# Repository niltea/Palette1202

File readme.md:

# Nilgiri12-02EC

English follows Japanese.

--------------------

Nilgiri12-02ECは、イラストレーターのための左手デバイスです。  
[Clip studio Paint](https://www.clipstudio.net) や、 [Adobe Photoshop](https://www.adobe.com/jp/products/photoshop.html)を使用した描画を快適に行うため設計されています。  
各種ショートカットを使用するためのキーを備えていることはもちろん、  
つまみを操作することで、ブラシサイズの変更やキャンバスの拡大・縮小等を快適に行うことができます。

コンパクトなサイズに設計されているため、持ち運んでの使用にも便利なだけでなく、  
据え置き環境で大型の液晶タブレットと一緒に使っても邪魔になりません。

また、オプションの電池キットを追加することで[BLE Micro Pro](https://yushakobo.jp/shop/ble-micro-pro/)にも対応するため、  
持ち運びの際でもケーブルが煩わしくありません。

Windows/Mac・Clip Studio / Photoshopの切替を行う事ができるため、  
PC・Macはもちろん、iPadでも同じ操作感で描画することができます。

--------------------

Nilgiri12-02EC is a lefthand-devece for illustrators. 
Designed for comfotablly drawing on [Clip studio Paint](https://www.clipstudio.net) / [Adobe Photoshop](https://www.adobe.com/jp/products/photoshop.html).

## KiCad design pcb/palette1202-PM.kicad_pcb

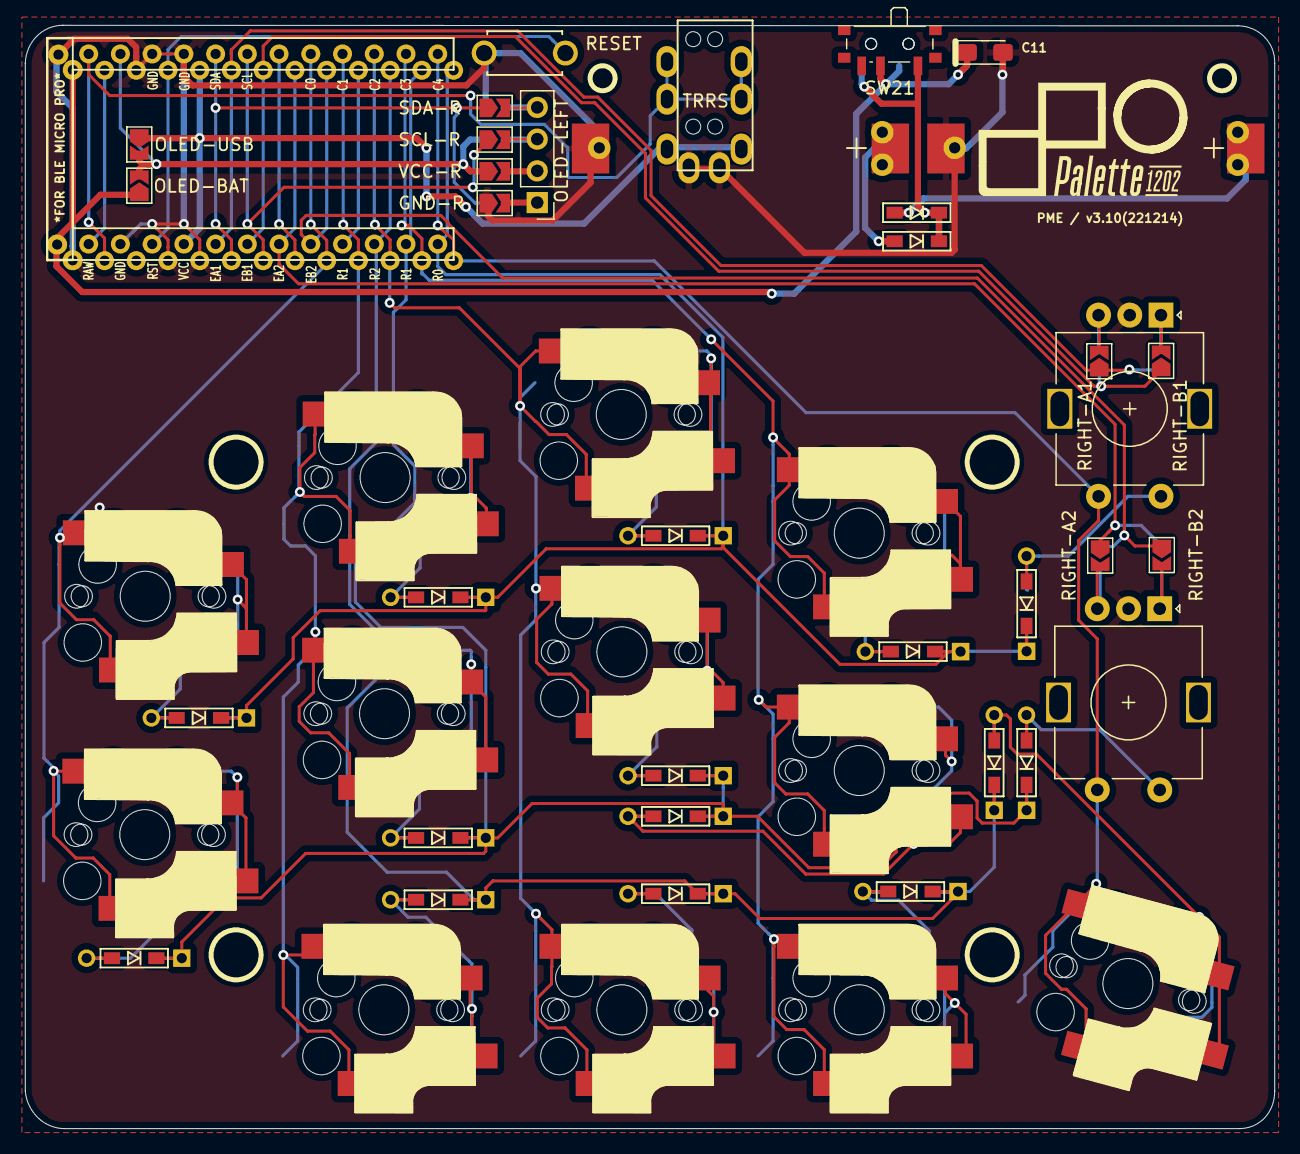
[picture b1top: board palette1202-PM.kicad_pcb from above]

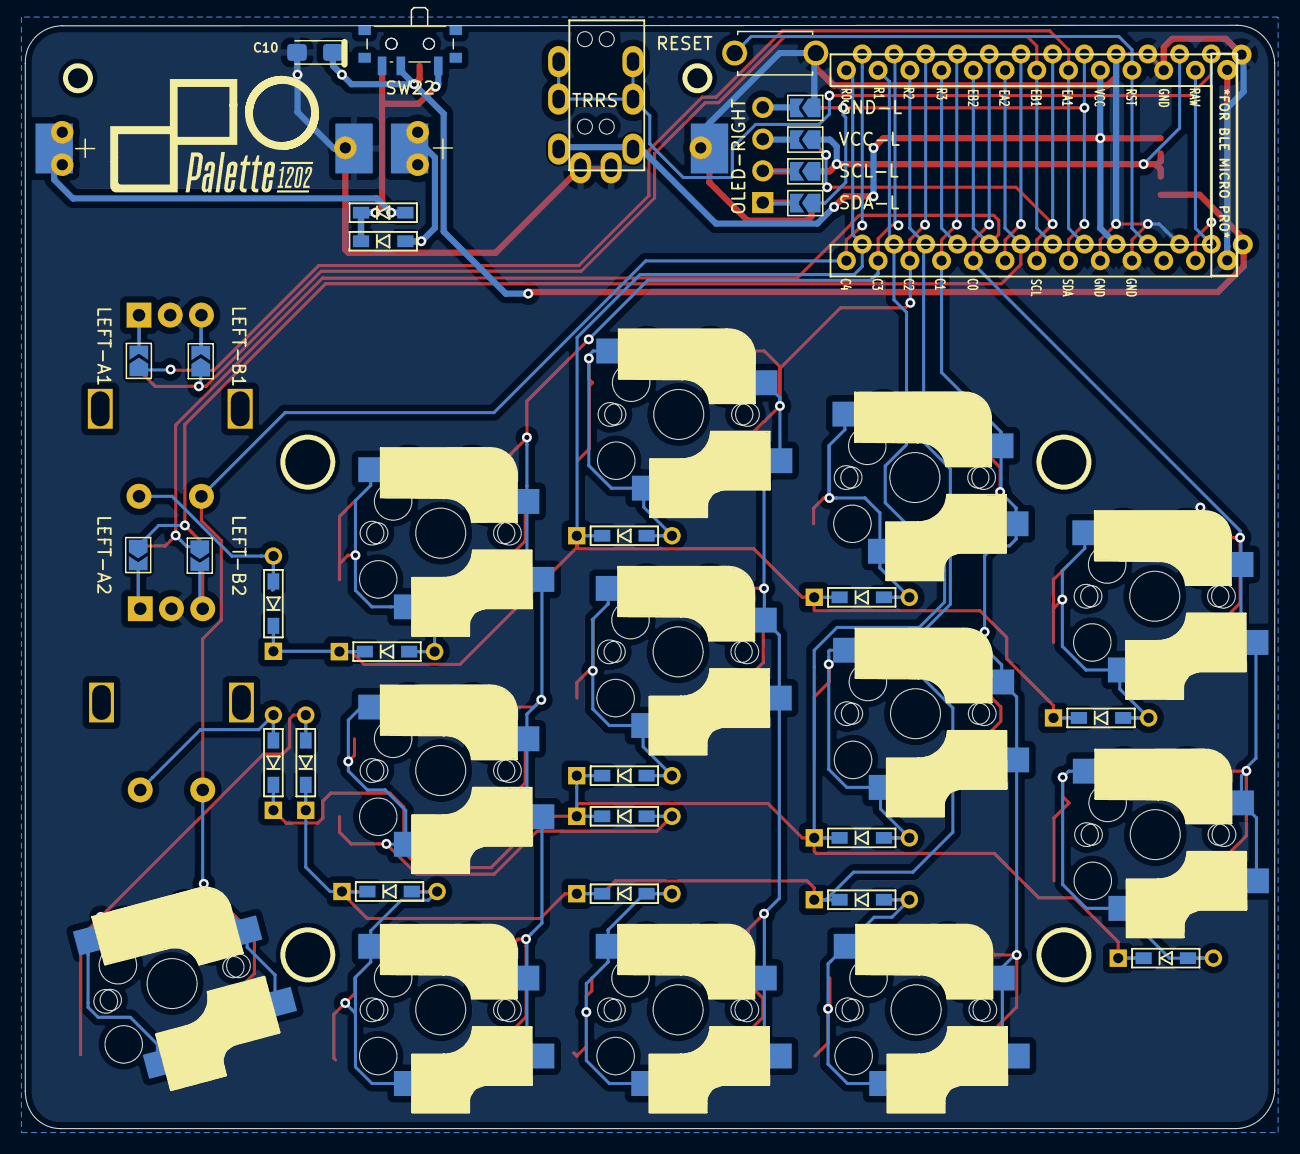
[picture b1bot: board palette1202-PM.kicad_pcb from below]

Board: 2 copper layers, 100.0 x 88.3 mm, 68 parts (26 on the bottom side), 45 nets.

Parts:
BT1, BT2: 3V; HU1632
C10, C11: 100u; CP_EIA-3216-10_Kemet-I_Pad1.58x1.35mm_HandSolder
D1, D2, D3, D4, D5, D6, D7, D8, D9, D10, D11, D12, D13, D14: 1N4148W; D3_TH_SMD
D30, D31: MBR120; D3_SMD
EC1, EC2: EC11E18244A5; RotaryEncoder_Alps_EC11E-Switch_Vertical_H20mm
GND-L: LEFT-GND; SolderJumper-2_P1.3mm_Open_TrianglePad1.0x1.5mm
GND-R: RIGHT-GND; SolderJumper-2_P1.3mm_Open_TrianglePad1.0x1.5mm
H1, H3: MountingHole; M2_vis
H5, H6, H7, H8: MountingHole; M2_spacer
J1: MJ-4PP-9
J10, J20: BAT+; Hole 0.8mm
J11, J21: BAT-; Hole 0.8mm
JP100: LEFT-A1; SolderJumper-2_P1.3mm_Open_TrianglePad1.0x1.5mm
JP101: LEFT-B1; SolderJumper-2_P1.3mm_Open_TrianglePad1.0x1.5mm
JP110: RIGHT-B1; SolderJumper-2_P1.3mm_Open_TrianglePad1.0x1.5mm
JP111: RIGHT-A1; SolderJumper-2_P1.3mm_Open_TrianglePad1.0x1.5mm
JP120: LEFT-A2; SolderJumper-2_P1.3mm_Open_TrianglePad1.0x1.5mm
JP121: LEFT-B2; SolderJumper-2_P1.3mm_Open_TrianglePad1.0x1.5mm
JP130: RIGHT-B2; SolderJumper-2_P1.3mm_Open_TrianglePad1.0x1.5mm
JP131: RIGHT-A2; SolderJumper-2_P1.3mm_Open_TrianglePad1.0x1.5mm
JP220: OLED-USB; SolderJumper-2_P1.3mm_Open_TrianglePad1.0x1.5mm
JP221: OLED-BAT; SolderJumper-2_P1.3mm_Open_TrianglePad1.0x1.5mm
OLED-LEFT: OLED; PinHeader_1x04_P2.54mm_Vertical
SCL-L: LEFT-SCL; SolderJumper-2_P1.3mm_Open_TrianglePad1.0x1.5mm
SCL-R: RIGHT-SCL; SolderJumper-2_P1.3mm_Open_TrianglePad1.0x1.5mm
SDA-L: LEFT-SDA; SolderJumper-2_P1.3mm_Open_TrianglePad1.0x1.5mm
SDA-R: RIGHT-SDA; SolderJumper-2_P1.3mm_Open_TrianglePad1.0x1.5mm
SW1, SW2, SW3, SW4, SW5, SW6, SW7, SW8, SW9, SW10, SW11, SW12: SW_PUSH; CherryMX_Choc_Hotswap
SW20: SW_RESET; ResetSW_1side
SW21, SW22: PWR; SW_SPDT_PCM12
U2: ProMicro; ProMicro_v2
VCC-L: LEFT-VCC; SolderJumper-2_P1.3mm_Open_TrianglePad1.0x1.5mm
VCC-R: RIGHT-VCC; SolderJumper-2_P1.3mm_Open_TrianglePad1.0x1.5mm

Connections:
Col0: SW1.1, SW2.1, U2.8 (5/C6)
Col1: SW3.1, SW4.1, SW5.1, U2.9 (6/D7)
Col2: SW6.1, SW7.1, SW8.1, U2.10 (7/E6)
Col3: SW9.1, SW10.1, SW11.1, U2.11 (8/B4)
Col4: EC1.S1, EC2.S1, SW12.1, U2.12 (9/B5)
DATA: J1.B, J1.C, U2.1 (TX0/D3)
GND: BT1.2 (-), BT2.2 (-), C10.2, C11.2, EC1.C, EC2.C, GND-L.1, GND-R.1, J1.A, J11.1, J21.1, SW20.1, U2.3 (GND), U2.4 (GND), U2.23 (GND)
LEFT: JP220.2 (B), JP221.2 (B), U2.2 (RX1/D2), VCC-L.1, VCC-R.1
unnamed: BT1.1 (+), D31.2 (A)
unnamed: BT2.1 (+), D30.2 (A)
unnamed: D1.2 (A), SW1.2
unnamed: D2.2 (A), SW2.2
unnamed: D3.2 (A), SW3.2
unnamed: D4.2 (A), SW4.2
unnamed: D5.2 (A), SW5.2
unnamed: D6.2 (A), SW6.2
unnamed: D7.2 (A), SW7.2
unnamed: D8.2 (A), SW8.2
unnamed: D9.2 (A), SW9.2
unnamed: D10.2 (A), SW10.2
unnamed: D11.2 (A), SW11.2
unnamed: D12.2 (A), SW12.2
unnamed: D13.2 (A), EC1.S2
unnamed: D14.2 (A), EC2.S2
unnamed: D30.1 (K), D31.1 (K), SW21.1 (A), SW22.1 (A)
unnamed: EC1.A, JP100.2, JP110.2
unnamed: EC1.B, JP101.2, JP111.2
unnamed: EC2.A, JP120.2, JP130.2
unnamed: EC2.B, JP121.2, JP131.2
unnamed: GND-R.2, OLED-LEFT.1, SDA-L.2
unnamed: OLED-LEFT.2, SCL-L.2, VCC-R.2
unnamed: OLED-LEFT.3, SCL-R.2, VCC-L.2
unnamed: GND-L.2, OLED-LEFT.4, SDA-R.2
RA1: JP100.1, JP111.1, U2.20 (F4/A3)
RA2: JP120.1, JP131.1, U2.18 (F6/A1)
RB1: JP101.1, JP110.1, U2.19 (F5/A2)
RB2: JP121.1, JP130.1, U2.17 (F7/A0)
RESET: SW20.2, U2.22 (RST)
Row0: D1.1 (K), D3.1 (K), D6.1 (K), D9.1 (K), D13.1 (K), U2.13 (B6/10)
Row1: D2.1 (K), D4.1 (K), D7.1 (K), D10.1 (K), D14.1 (K), U2.14 (B2/16)
Row2: D5.1 (K), D8.1 (K), D11.1 (K), D12.1 (K), U2.15 (B3/14)
SCL: SCL-L.1, SCL-R.1, U2.6 (3/D0/SCL)
SDA: SDA-L.1, SDA-R.1, U2.5 (2/D1/SDA)
VCC: J1.D, JP220.1 (A), U2.21 (VCC)
Vbat: C10.1, C11.1, J10.1, J20.1, JP221.1 (A), SW21.2 (B), SW22.2 (B)

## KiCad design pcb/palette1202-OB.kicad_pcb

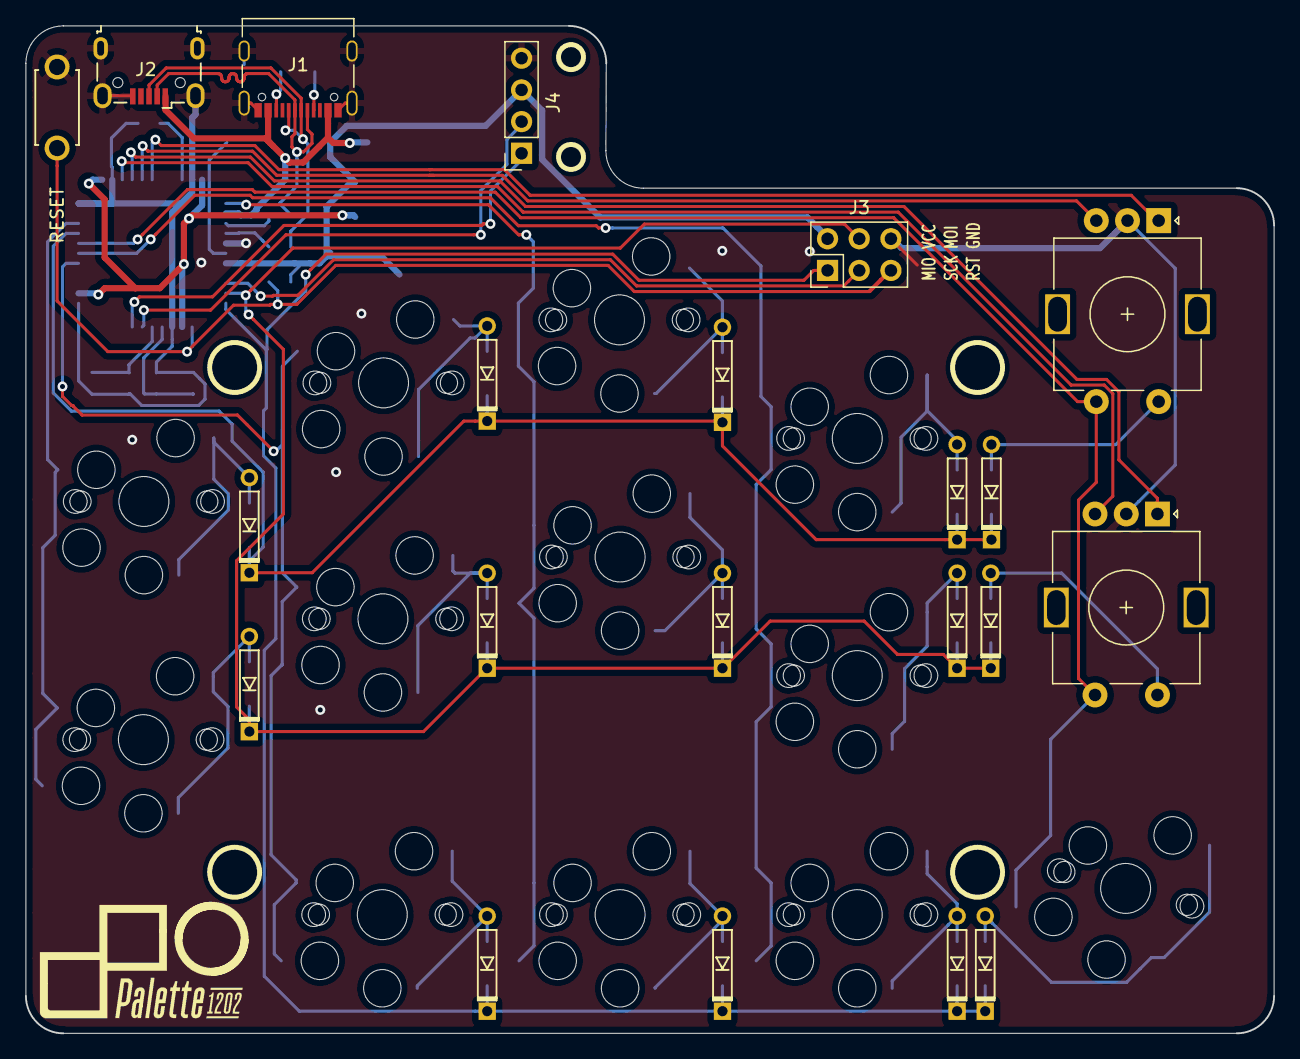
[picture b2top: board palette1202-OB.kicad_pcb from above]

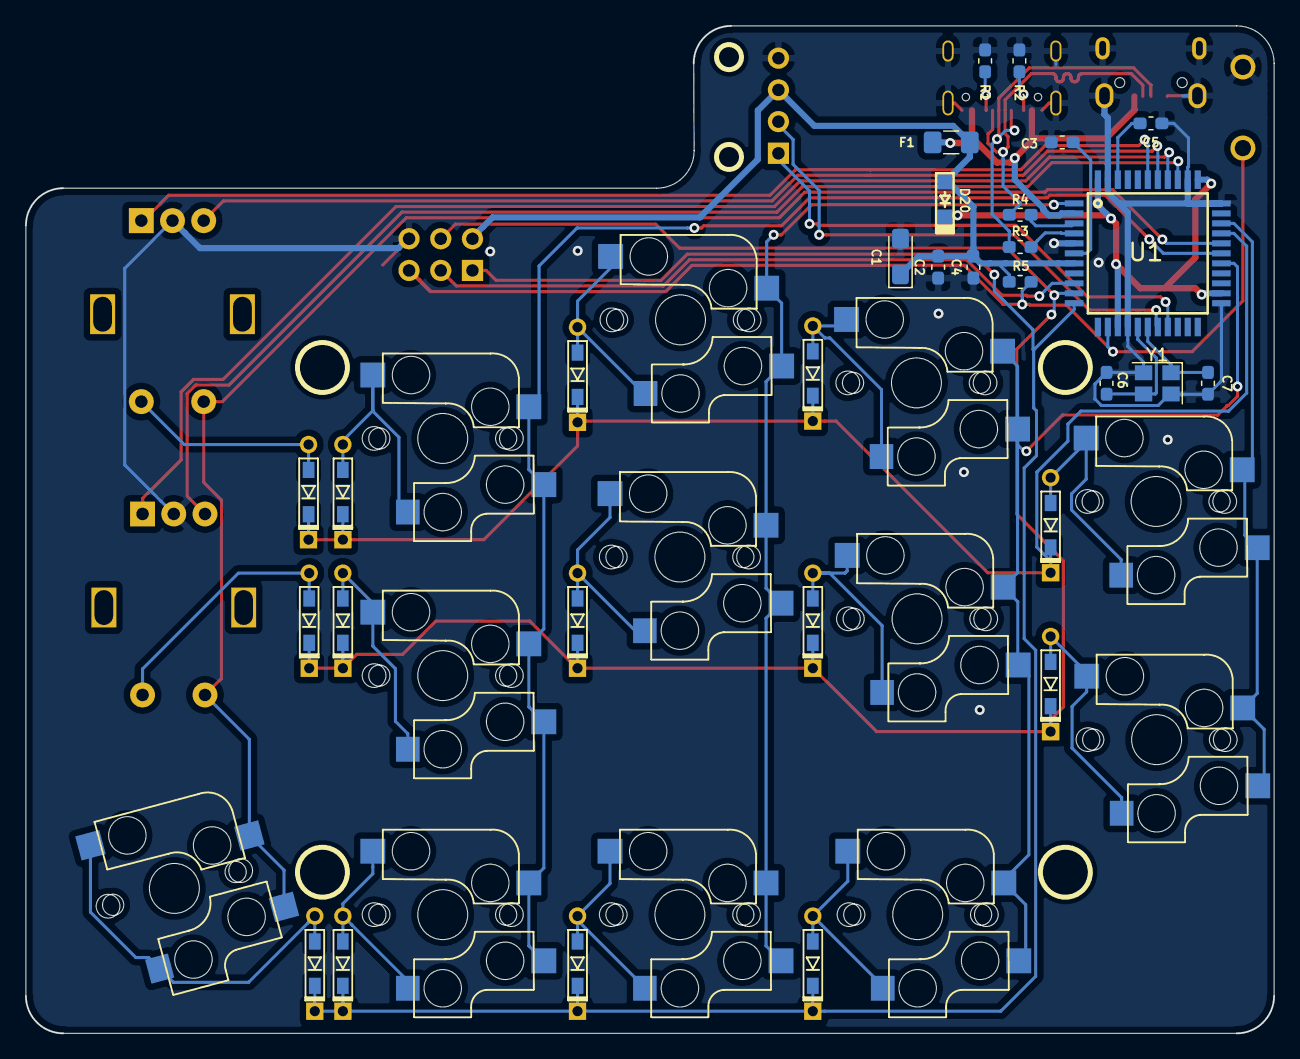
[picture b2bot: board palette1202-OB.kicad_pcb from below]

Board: 2 copper layers, 100.0 x 80.7 mm, 55 parts (30 on the bottom side), 44 nets.

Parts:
C1: 10u; CP_EIA-3216-10_Kemet-I_Pad1.58x1.35mm_HandSolder
C2, C3: 1u; C_0603_1608Metric_Pad1.05x0.95mm_HandSolder
C4, C5: 0.1u; C_0603_1608Metric_Pad1.05x0.95mm_HandSolder
C6, C7: 22p; C_0603_1608Metric_Pad1.05x0.95mm_HandSolder
D1, D2, D3, D4, D5, D6, D7, D8, D9, D10, D11, D12, D13, D14: 1N4148W; D3_TH_SMD
D20: MBR120; D_SOD123F
EC1, EC2: EC11E18244A5; RotaryEncoder_Alps_EC11E-Switch_Vertical_H20mm
F1: 500mA; Fuse_1206_3216Metric_Pad1.42x1.75mm_HandSolder
H1, H3: MountingHole; M2_vis
H5, H6, H7, H8: MountingHole; M2_spacer
J1: USB-C; USB_C_Receptacle_Palconn_UTC16-G
J2: USB_B_Micro; USB_Micro-B_Wuerth_629105150521
J3: ISP; PinHeader_2x03_P2.54mm_Vertical
J4: OLED; PinSocket_1x04_P2.54mm_Vertical
R1, R2: 5.1k; R_0603_1608Metric_Pad1.05x0.95mm_HandSolder
R3, R4: 22; R_0603_1608Metric_Pad1.05x0.95mm_HandSolder
R5: 10k; R_0603_1608Metric_Pad1.05x0.95mm_HandSolder
SW1, SW2, SW3, SW4, SW5, SW6, SW7, SW8, SW9, SW10, SW11, SW12: SW_PUSH; CherryMX_Choc_Hotswap-1Side
SW20: SW_RESET; ResetSW_1side
U1: ATmega32U4-AU; ATMEGA32U4-AU
Y1: 16MHz; Crystal_SMD_3225-4Pin_3.2x2.5mm

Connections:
Col0: SW1.1, SW2.1, U1.31
Col1: SW3.1, SW4.1, SW5.1, U1.27
Col2: SW6.1, SW7.1, SW8.1, U1.1
Col3: SW9.1, SW10.1, SW11.1, U1.28
Col4: EC1.S1, EC2.S1, SW12.1, U1.29
D+: J1.A6, J1.B6, J2.3, R3.2
D-: J1.A7, J1.B7, J2.2, R4.2
GND: C1.2, C2.2, C3.2, C4.2, C5.2, C6.2, C7.1, EC1.C, EC2.C, J1.A1, J1.A12, J1.B1, J1.B12, J1.S1, J2.5, J2.6, J3.6, J4.4, R1.1, R2.1, SW20.1, U1.5, U1.15, U1.23, U1.33, U1.35, U1.43, Y1.2, Y1.4
MISO: D5.1, D8.1, D11.1, D12.1, J3.1, U1.11
MOSI: D2.1, D4.1, D7.1, D10.1, D14.1, J3.4, U1.10
unnamed: C3.1, U1.6
unnamed: C5.1, U1.42
unnamed: C6.1, U1.16, Y1.3
unnamed: C7.2, U1.17, Y1.1
unnamed: D1.2, SW1.2
unnamed: D2.2, SW2.2
unnamed: D3.2, SW3.2
unnamed: D4.2, SW4.2
unnamed: D5.2, SW5.2
unnamed: D6.2, SW6.2
unnamed: D7.2, SW7.2
unnamed: D8.2, SW8.2
unnamed: D9.2, SW9.2
unnamed: D10.2, SW10.2
unnamed: D11.2, SW11.2
unnamed: D12.2, SW12.2
unnamed: D13.2, EC1.S2
unnamed: D14.2, EC2.S2
unnamed: D20.1, U1.14, U1.24, U1.34, U1.44
unnamed: J1.A5, R1.2
unnamed: J1.B5, R2.2
unnamed: R3.1, U1.4
unnamed: R4.1, U1.3
RA1: EC1.A, U1.39
RA2: EC2.A, U1.37
RB1: EC1.B, U1.38
RB2: EC2.B, U1.36
RESET: J3.5, R5.2, SW20.2, U1.13
Row0: D1.1, D3.1, D6.1, D9.1, D13.1, U1.30
SCK: J3.3, U1.9
SCL: J4.2, U1.18
SDA: J4.1, U1.19
VBUS: F1.2, J1.A4, J1.A9, J1.B4, J1.B9, J2.1, U1.2
VCC: C1.1, C2.1, C4.1, D20.2, F1.1, J3.2, J4.3, R5.1, U1.7

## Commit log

2019-09-27 first
2019-10-24 addede BOM(WIP)
2019-10-25 merged onboard type / added footprints
2019-10-26 combined Onboard type and Pro Micro type
2019-10-29 全体調整
2019-10-29 gerberファイル再出力
2019-11-03 moved PCBs to their dir
2019-11-15 edited readme
2019-11-15 added key footprints
2019-11-24 rm unused
2019-11-24 fixed front panel
2019-11-24 revised footprint
2019-11-24 updated Ai Data
2019-11-24 updated normal PCB
2019-11-24 added onboard PCB
2019-11-24 rm hot-swap ver
2019-11-24 added logo
2019-11-24 renamed files
2019-11-24 added back plate(OB)
2019-11-24 revised annotation, BOM, etc.
2019-11-24 output gerber
2019-12-29 add BLE
2019-12-29 added PCB Exported SVG
2019-12-29 fixed panels
2019-12-29 add logo
2019-12-29 added image
2020-01-27 revised BLE Firmware
2020-03-29 updated main board
2020-03-29 renamed front
2020-03-29 updated front panel
2020-03-29 updated back panel
2020-03-29 export gerber
2020-03-30 updated panel
2020-03-30 updated docs
2020-04-15 moved BLE firmware src directory
2020-04-15 fix BLE firm for iOS
2020-06-29 revised cover panel
2022-12-01 added connecter for split layout(testing)
2022-12-14 minor fix, etc.
